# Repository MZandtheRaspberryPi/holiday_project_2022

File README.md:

# holiday_project_2022

A group of friends got together around the holidays in 2022 to build a fun electronics project in 4 weeks. We decided to build a bat that had some RGB lights, some ultrasound sensors, and a oled for a face.  

This involved designing the bat model and 3d-printing it, working on a software package to drive all the electronics and figure out when something was in front of the bat, and desiging hardware and a PCB to make connecting the electronics easy. You can find more details on each of these in the subfolders design, hardware, and firmware.  

Here are all the parts:  

We had a pizza party and built 5 of them:

Heres what the back looks like assembled:

This is what the bat is seeing, ie the signal it is sampling and getting from its transducer which is listening:

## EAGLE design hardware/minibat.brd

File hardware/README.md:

# Hardware

We first brainstormed what components we needed. We wanted to visualize the face, and were deciding between LED Matrix and a screen. We went for an OLED Screen to have better resolution for expressions and animations. We also wanted lights in the wings, and quickly decided on RGB Addressable LEDs. We also wanted ultrasound sensors, and decided eventually on a transducer and complementary circuit.  

From there, it made sense to make a custom PCB to bring it all together. We designed and got the order out quickly, to accomodate shipping times from China. We used only through-hole components to make it easier to solder. You can find a list of components in the BOM.xls file in the repo. If you wanted to order your own, you can find the CAM zipped file in the CAM folder, and can upload that to most fabrication sites.  

An assembly plan is included here. Some of the components were unnescessary, and so we crossed those off in red in the images:

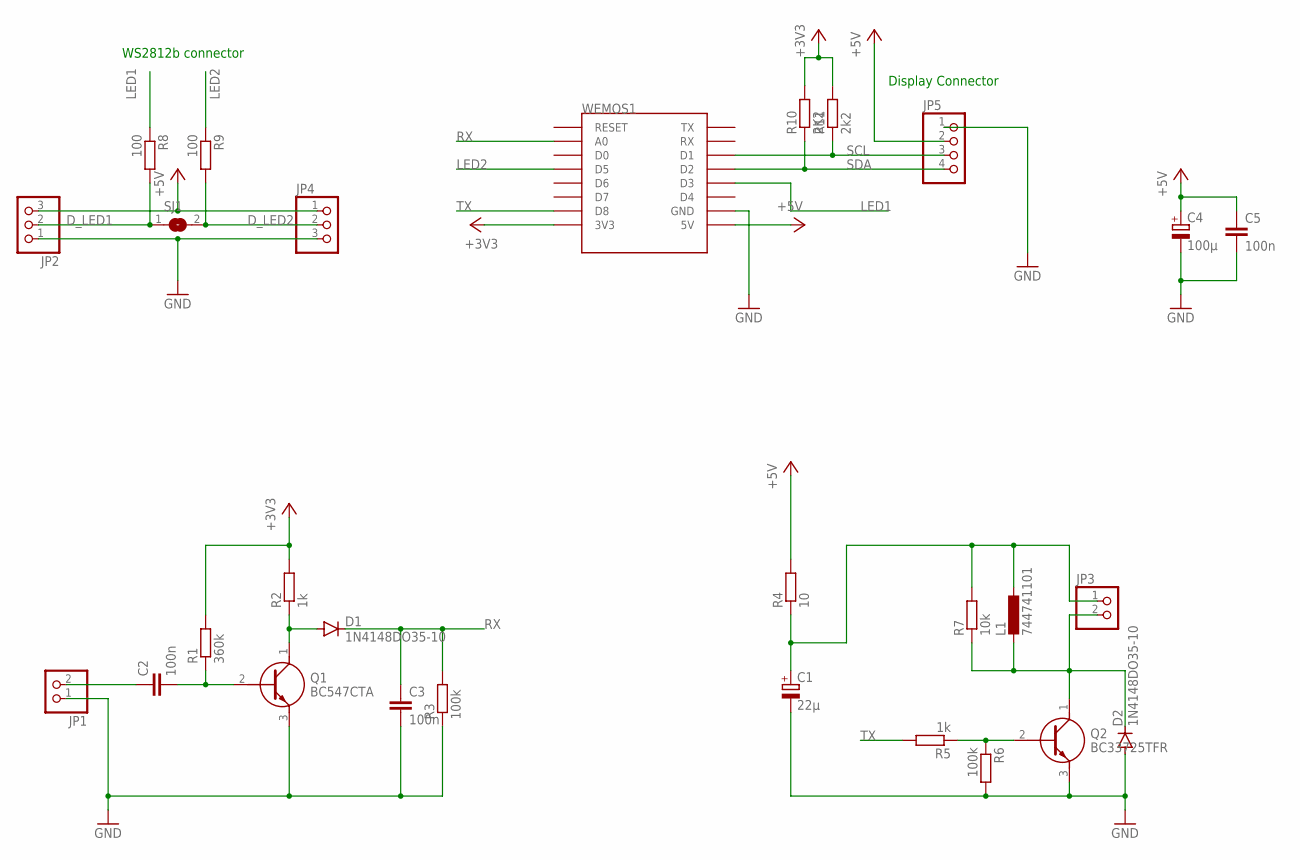
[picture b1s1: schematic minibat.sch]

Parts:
C1: 22µ; E5-8,5
C2, C3, C5: 100n; C050-035X075
C4: 100µ; E5-8,5
D1, D2: 1N4148DO35-10; DO35-10
JP1, JP3: PINHD-1X2; 1X02
JP2, JP4: PINHD-1X3; 1X03
JP5: PINHD-1X4; 1X04
L1: 744741101; 6000-XXXX-RC
Q1: BC547CTA; MC79L15ACPG
Q2: BC33725TFR
R1: 360k; 0207/10
R2, R5: 1k; 0207/10
R3, R6: 100k; 0207/10
R4: 10; 0207/10
R7: 10k; 0207/10
R8, R9: 100; 0207/10
R10: 2K2; 0207/10
R11: 2k2; 0207/10
SJ1: SJ
WEMOS1: WEMOS-D1-MINI

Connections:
+3V3: R1.2, R2.2, R10.2, R11.2, WEMOS1.3V3
+5V: C4.+, C5.1, JP2.3, JP4.1, JP5.2, R4.2, WEMOS1.5V
D_LED1: JP2.2, R8.2, SJ1.1
D_LED2: JP4.2, R9.2, SJ1.2
GND: C1.-, C3.2, C4.-, C5.2, D2.A, JP1.1, JP2.1, JP4.3, JP5.1, Q1.3 (E), Q2.3 (E), R3.1, R6.2, WEMOS1.GND
LED1: R8.1, WEMOS1.D3
LED2: R9.1, WEMOS1.D5
unnamed: C2.1, JP1.2
unnamed: D1.A, Q1.1 (C), R2.1
unnamed: C2.2, Q1.2 (B), R1.1
unnamed: C1.+, JP3.1, L1.1, R4.1, R7.2
unnamed: D2.C, JP3.2, L1.2, Q2.1 (C), R7.1
unnamed: Q2.2 (B), R5.1, R6.1
RX: C3.1, D1.C, R3.2, WEMOS1.A0
SCL: JP5.3, R11.1, WEMOS1.D1
SDA: JP5.4, R10.1, WEMOS1.D2
TX: R5.2, WEMOS1.D8

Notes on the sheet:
Display Connector
WS2812b connector

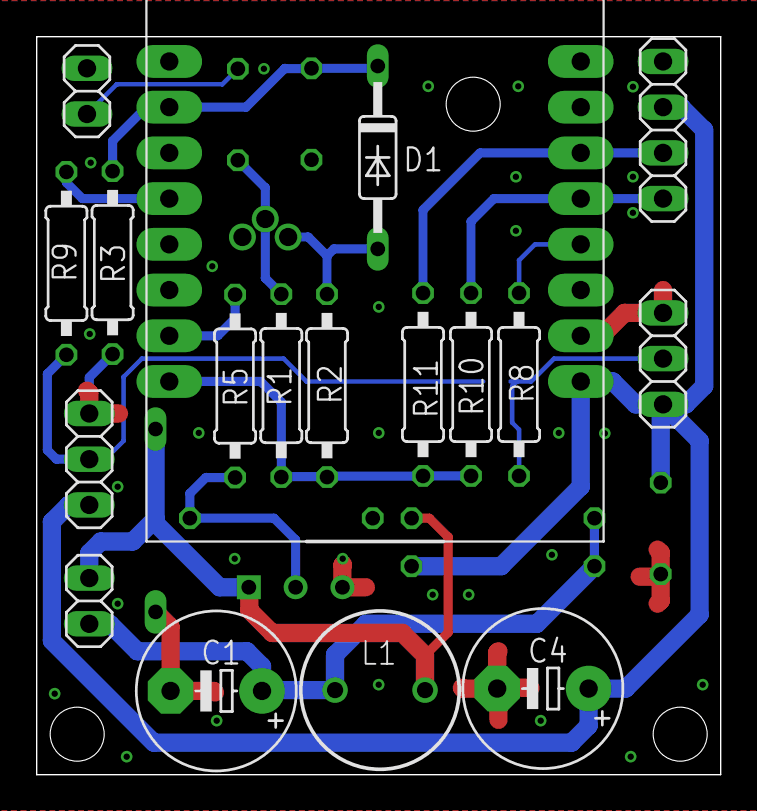
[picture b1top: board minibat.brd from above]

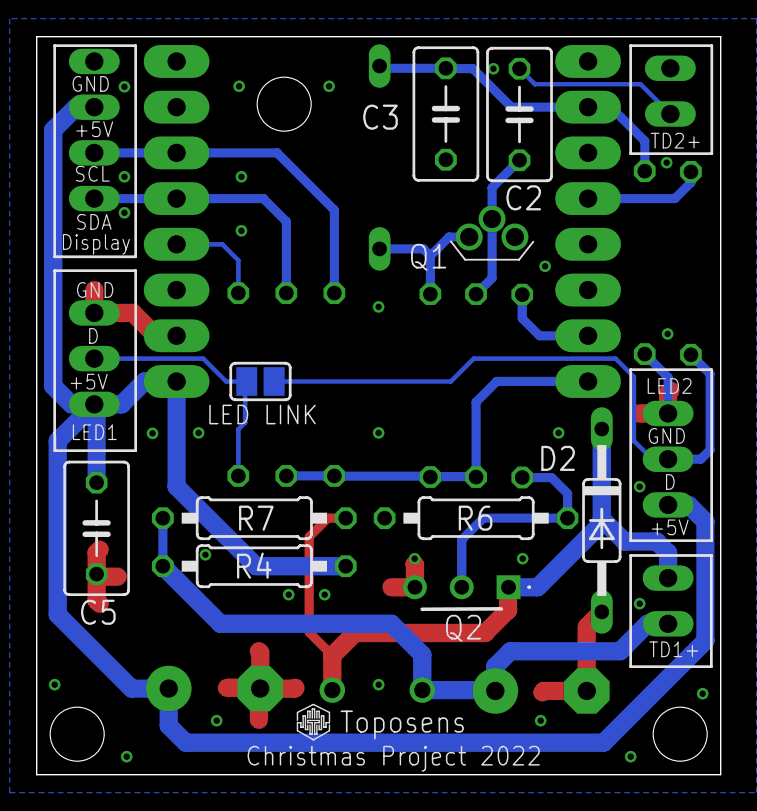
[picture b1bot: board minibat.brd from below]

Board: 2 copper layers, 38.0 x 41.0 mm, 28 parts (10 on the bottom side), 17 nets.

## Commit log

2022-11-16 initial planning commit
2022-11-16 adding image to plan
2022-11-16 updating image path
2022-11-16 adding notes
2022-11-16 adding ideas and such
2022-11-18 updating brainstorm spreadsheet
2022-11-21 updating docs
2022-11-22 updating readme to include planning docs
2022-11-22 making line seperation
2022-11-23 adding budget
2022-11-25 adding hardware, updating budget
2022-12-01 firmware initial commit
2022-12-01 add basic text to oled
2022-12-05 updating budget
2022-12-05 add transducer task
2022-12-05 add second board config
2022-12-10 use d1 mini and increase upload speed
2022-12-10 add led modes and use d1 mini pins
2022-12-10 add basic presence detection
2022-12-10 add display of adc values
2022-12-11 add action mode
2022-12-11 edit sparkling mode
2022-12-12 edit data plot
2022-12-12 add adc plot mode
2022-12-13 adding README.md
2022-12-13 adding facial animations
2022-12-13 adding cad
2022-12-14 put face animation to separate file
2022-12-14 making suprise animation for active mode
2022-12-14 update face animation time
2022-12-14 adjusting timings
2022-12-15 use preamplifier
2022-12-16 adding docs
